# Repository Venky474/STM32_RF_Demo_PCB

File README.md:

# STM32_RF_Demo_PCB

This is a custom STM32 RF PCB designed using KiCad.

## Contents
- 🧩 KiCad Project Files (`.kicad_pro`, `.kicad_pcb`, `.kicad_sch`)
- 📦 Gerber Files (in `.rar`)
- 📄 BOM: `BOM_Output.csv`
- 🤖 Pick and Place: `STM32_RF.cpl`

## Preview

Preview of the STM32_RF PCB layout (generated using KiCad 3D viewer).

## License
[MIT](LICENSE) or specify your own

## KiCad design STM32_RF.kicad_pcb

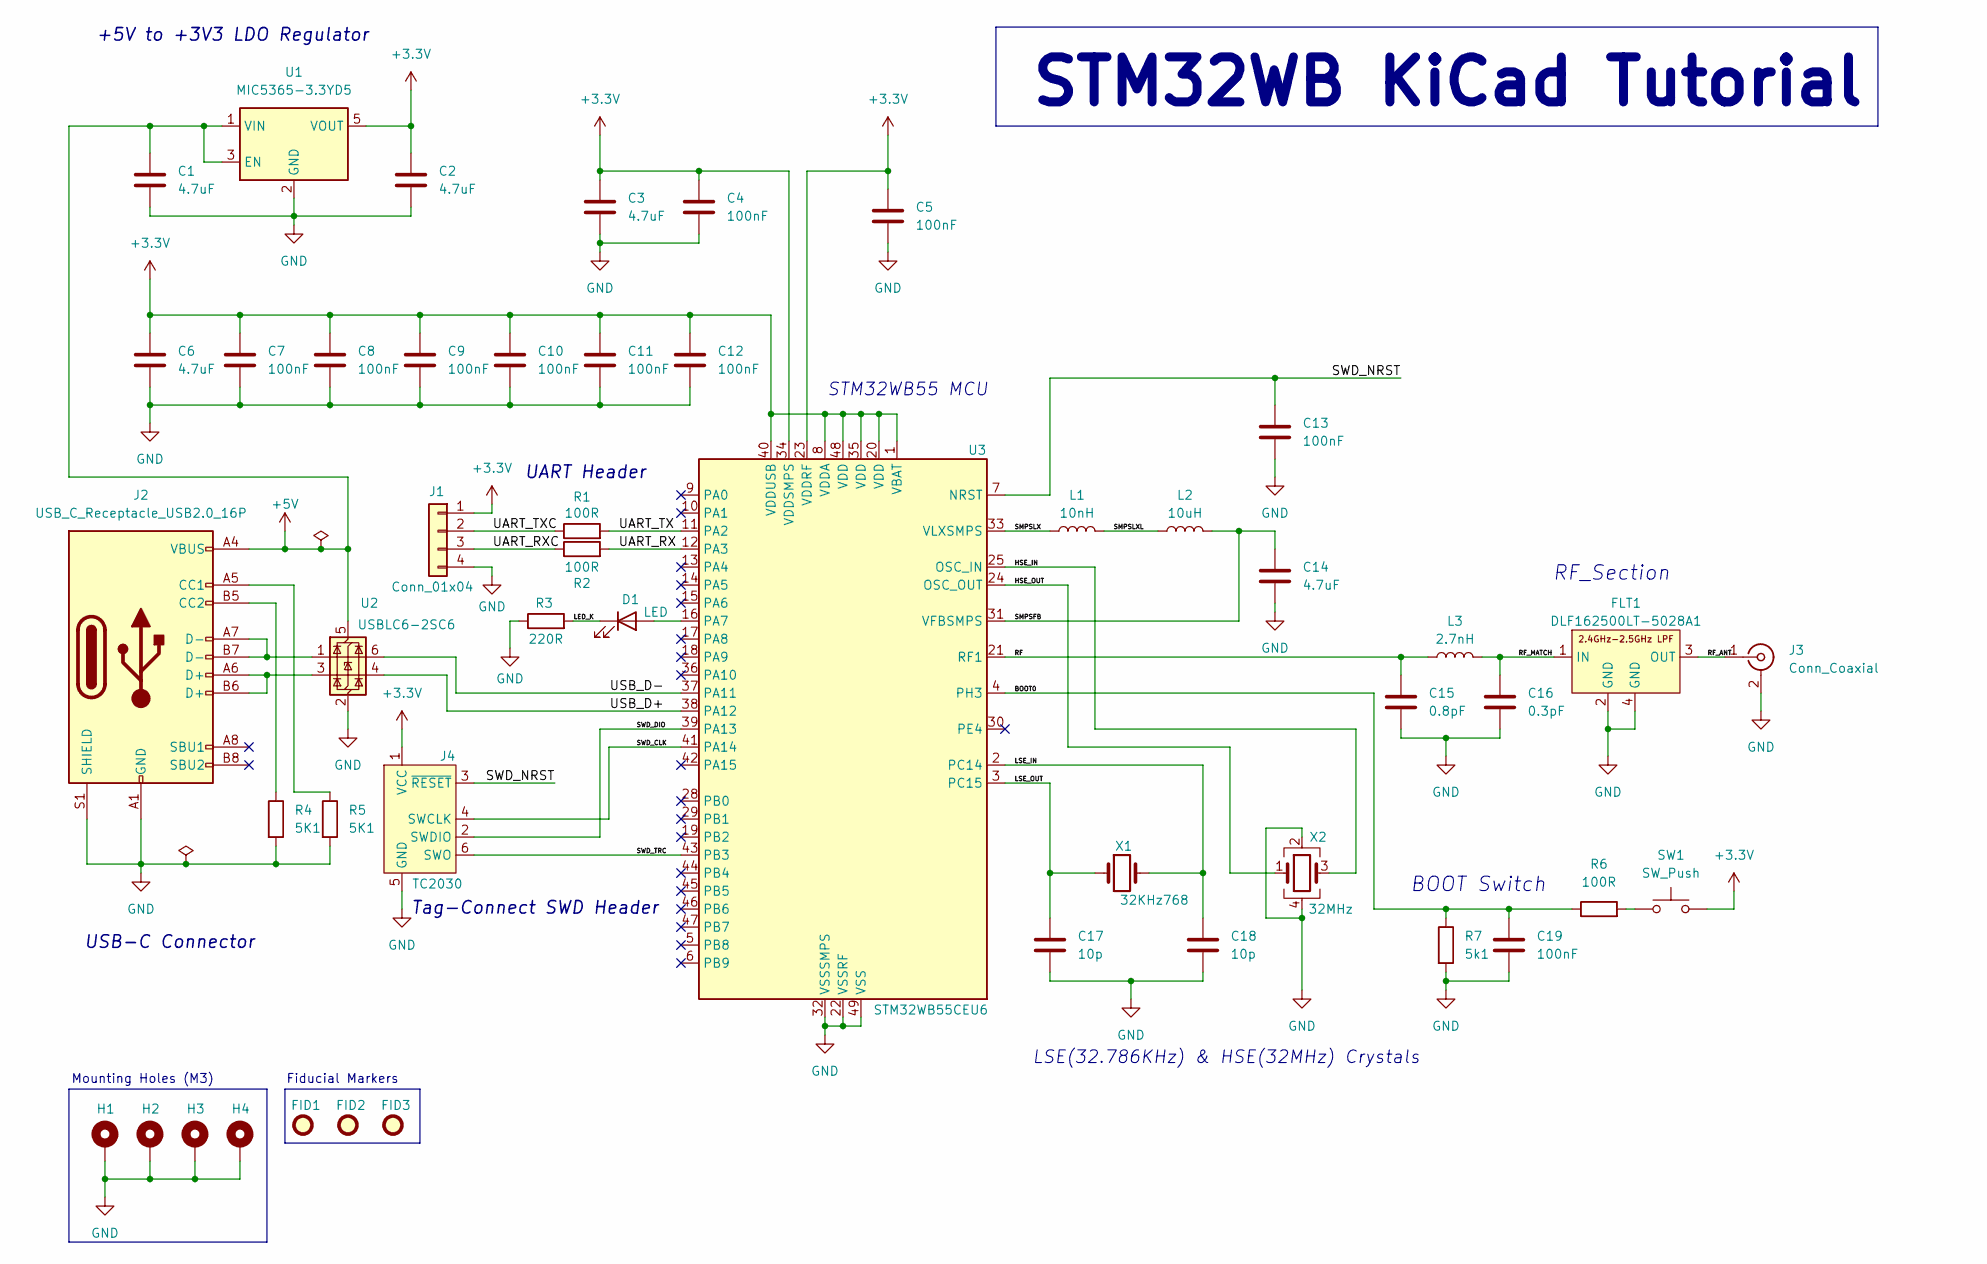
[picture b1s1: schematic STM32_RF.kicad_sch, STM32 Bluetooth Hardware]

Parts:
C1, C2, C3, C6, C14: 4.7uF; C_0603_1608Metric
C4, C5, C7, C8, C9, C10, C11, C12, C13, C19: 100nF; C_0402_1005Metric
C15: 0.8pF; C_0402_1005Metric
C16: 0.3pF; C_0402_1005Metric
C17, C18: 10p; C_0402_1005Metric
D1: LED; C_0402_1005Metric
FID1, FID2, FID3: Fiducial; Fiducial_1mm_Mask2mm
FLT1: DLF162500LT-5028A1; Untitled
H1: MountingHole_Pad; MountingHole_3.2mm_M3_Pad
H2, H3, H4: MountingHole_Pad; MountingHole_2.2mm_M2_Pad_Via
J1: Conn_01x04; Molex_PicoBlade_53048-0410_1x04_P1.25mm_Horizontal
J2: USB_C_Receptacle_USB2.0_16P; USB_C_Receptacle_GCT_USB4105-xx-A_16P_TopMnt_Horizontal
J3: Conn_Coaxial; U.FL_Hirose_U.FL-R-SMT-1_Vertical
J4: TC2030; Tag-Connect_TC2030-IDC-FP_2x03_P1.27mm_Vertical
L1: 10nH; L_0402_1005Metric
L2: 10uH; L_0805_2012Metric
L3: 2.7nH; L_0402_1005Metric
R1, R2, R6: 100R; C_0402_1005Metric
R3: 220R; C_0402_1005Metric
R4, R5: 5K1; C_0402_1005Metric
R7: 5k1; C_0402_1005Metric
SW1: SW_Push; SW_Tactile_SPST_NO_Straight_CK_PTS636Sx25SMTRLFS
U1: MIC5365-3.3YD5; SOT-23-5
U2: USBLC6-2SC6; SOT-23-6
U3: STM32WB55CEU6; QFN-48-1EP_7x7mm_P0.5mm_EP5.6x5.6mm
X1: 32KHz768; Crystal_SMD_2012-2Pin_2.0x1.2mm
X2: 32MHz; Crystal_SMD_2016-4Pin_2.0x1.6mm

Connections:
+3.3V: C2.1, C3.1, C4.1, C5.1, C6.1, C7.1, C8.1, C9.1, C10.1, C11.1, C12.1, J1.1, J4.1 (VCC), SW1.2, U1.5 (VOUT), U3.1 (VBAT), U3.8 (VDDA), U3.20 (VDD), U3.23 (VDDRF), U3.34 (VDDSMPS), U3.35 (VDD), U3.40 (VDDUSB), U3.48 (VDD)
+5V: C1.1, J2.A4 (VBUS), J2.A9 (VBUS), J2.B4 (VBUS), J2.B9 (VBUS), U1.1 (VIN), U1.3 (EN), U2.5 (VBUS)
/BOOT0: C19.1, R6.1, R7.1, U3.4 (PH3)
/HSE_IN: U3.25 (OSC_IN), X2.3
/HSE_OUT: U3.24 (OSC_OUT), X2.1
/LED_K: D1.1 (K), R3.2
/LSE_IN: C18.1, U3.2 (PC14), X1.2
/LSE_OUT: C17.1, U3.3 (PC15), X1.1
/RF: C15.1, L3.1, U3.21 (RF1)
/RF_ANT: FLT1.3 (OUT), J3.1 (In)
/RF_MATCH: C16.1, FLT1.1 (IN), L3.2
/SMPSFB: C14.1, L2.2, U3.31 (VFBSMPS)
/SMPSLX: L1.1, U3.33 (VLXSMPS)
/SMPSLXL: L1.2, L2.1
/SWD_CLK: J4.4 (SWCLK), U3.41 (PA14)
/SWD_DIO: J4.2 (SWDIO), U3.39 (PA13)
/SWD_NRST: C13.1, J4.3 (~RESET), U3.7 (NRST)
/SWD_TRC: J4.6 (SWO), U3.43 (PB3)
/UART_RX: R2.2, U3.12 (PA3)
/UART_RXC: J1.3, R2.1
/UART_TX: R1.2, U3.11 (PA2)
/UART_TXC: J1.2, R1.1
/USB_D+: U2.4 (I/O2), U3.38 (PA12)
/USB_D-: U2.6 (I/O1), U3.37 (PA11)
GND: C1.2, C2.2, C3.2, C4.2, C5.2, C6.2, C7.2, C8.2, C9.2, C10.2, C11.2, C12.2, C13.2, C14.2, C15.2, C16.2, C17.2, C18.2, C19.2, FLT1.2 (GND), FLT1.4 (GND), H1.1, H2.1, H3.1, H4.1, J1.4, J2.A1 (GND), J2.A12 (GND), J2.B1 (GND), J2.B12 (GND), J2.S1 (SHIELD), J3.2 (Ext), J4.5 (GND), R3.1, R4.2, R5.2, R7.2, U1.2 (GND), U2.2 (GND), U3.22 (VSSRF), U3.32 (VSSSMPS), U3.49 (VSS), X2.2, X2.4
unnamed: D1.2 (A), U3.16 (PA7)
unnamed: J2.A5 (CC1), R5.1
unnamed: J2.B5 (CC2), R4.1
unnamed: J2.A6 (D+), J2.B6 (D+), U2.3 (I/O2)
unnamed: J2.A7 (D-), J2.B7 (D-), U2.1 (I/O1)
unnamed: R6.2, SW1.1

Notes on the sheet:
STM32WB KiCad Tutorial
STM32WB55 MCU
Fiducial Markers
Tag-Connect SWD Header
UART Header
Mounting Holes (M3)
RF_Section
+5V to +3V3 LDO Regulator
USB-C Connector
BOOT Switch
LSE(32.786KHz) & HSE(32MHz) Crystals

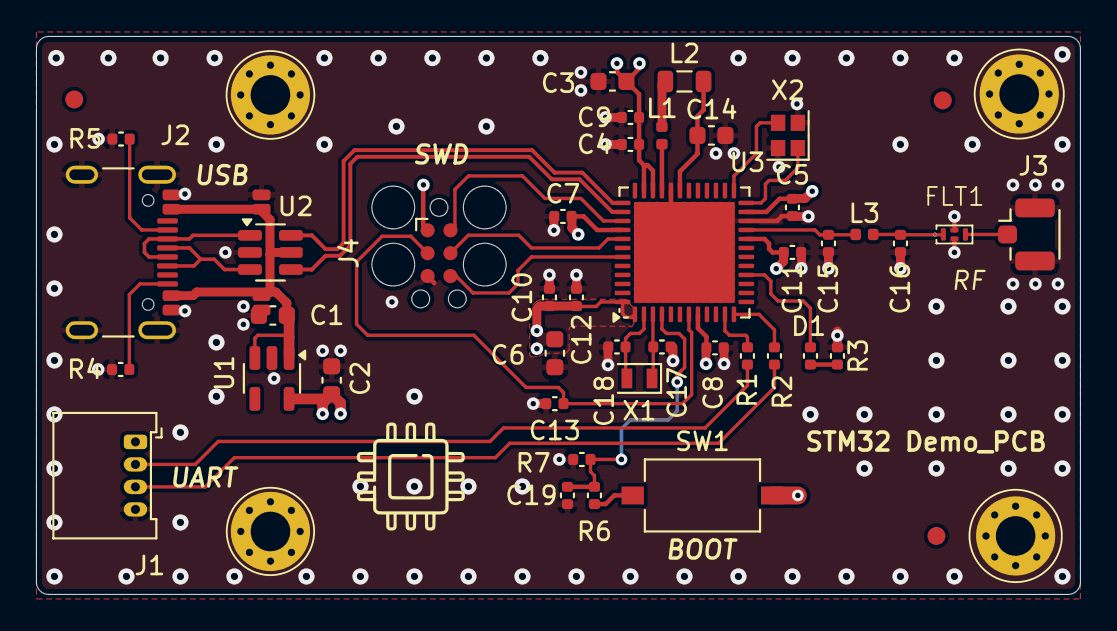
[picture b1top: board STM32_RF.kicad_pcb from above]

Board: 4 copper layers, 58.0 x 31.0 mm, 49 parts (0 on the bottom side), 31 nets.

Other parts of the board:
G: LOGO

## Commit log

2025-06-26 README.md
2025-06-26 Add files via upload
    3D image of PCB
